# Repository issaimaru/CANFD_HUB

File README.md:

# CANFD_HUB
CANFDコントローラ「ひなた」用のハブ<br>
<br>

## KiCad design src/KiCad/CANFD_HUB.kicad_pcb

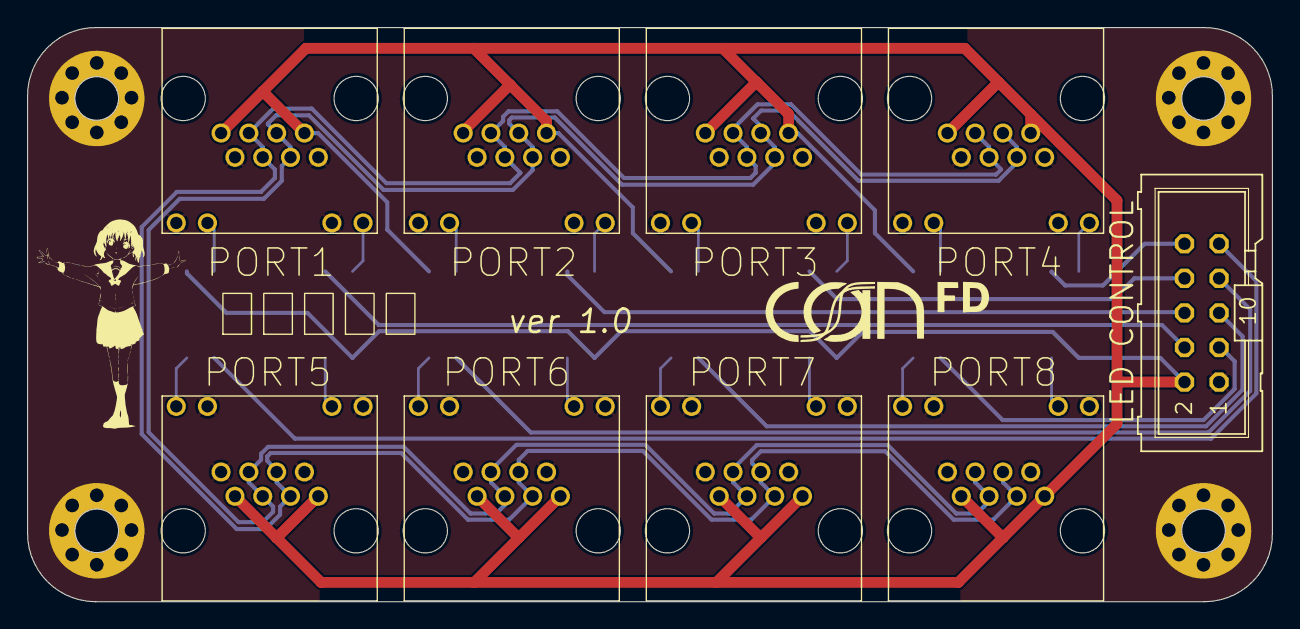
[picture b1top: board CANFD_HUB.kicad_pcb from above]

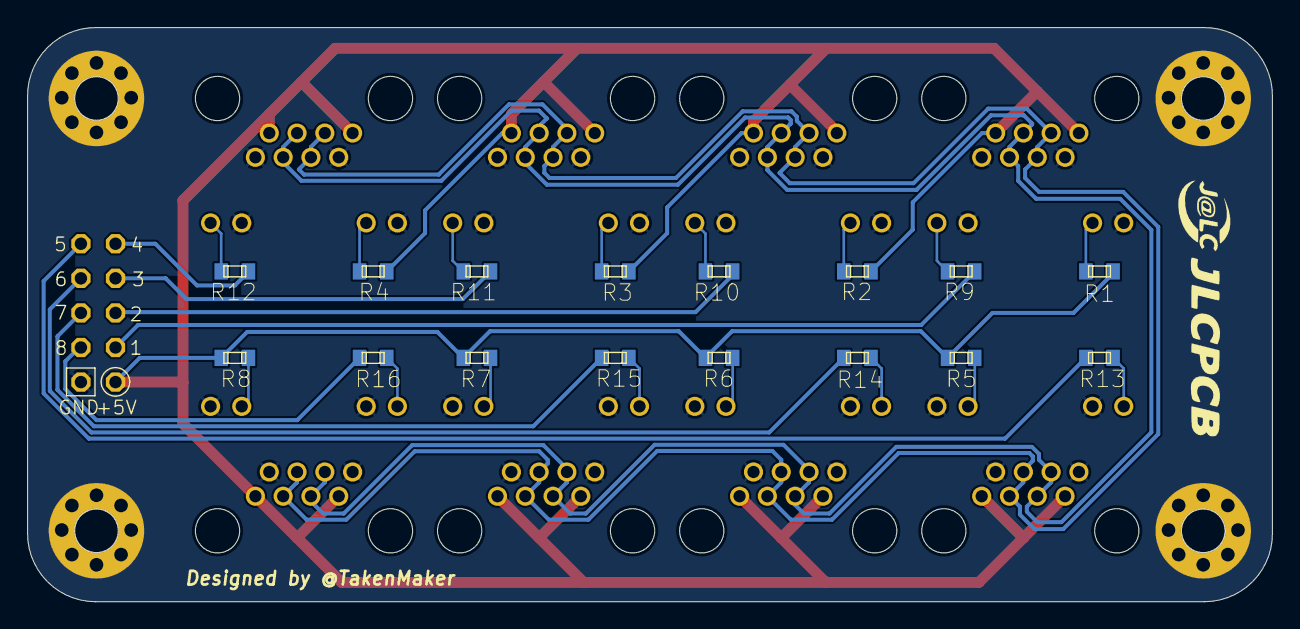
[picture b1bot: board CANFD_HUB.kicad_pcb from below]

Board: 2 copper layers, 91.4 x 42.2 mm, 29 parts (16 on the bottom side), 28 nets.

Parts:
H1, H2, H3, H4: MOUNT-HOLE3.2(NORESIST); 3,2
LED CONTROL: ML10
PORT1, PORT2, PORT3, PORT4, PORT5, PORT6, PORT7, PORT8: MTJ-88ARX1-LH
R1: R1; CR0603
R2: R2; CR0603
R3: R3; CR0603
R4: R4; CR0603
R5: R5; CR0603
R6: R6; CR0603
R7: R7; CR0603
R8: R8; CR0603
R9: R9; CR0603
R10: R10; CR0603
R11: R11; CR0603
R12: R12; CR0603
R13: R13; CR0603
R14: R14; CR0603
R15: R15; CR0603
R16: R16; CR0603

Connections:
+5V: LED CONTROL.2, PORT1.1, PORT1.7, PORT2.1, PORT2.7, PORT3.1, PORT3.7, PORT4.1, PORT4.7, PORT5.1, PORT5.7, PORT6.1, PORT6.7, PORT7.1, PORT7.7, PORT8.1, PORT8.7, R1.RIGHT, R2.RIGHT, R3.RIGHT, R4.RIGHT, R5.RIGHT, R6.RIGHT, R7.RIGHT, R8.RIGHT
CAN_H+: PORT1.5, PORT1.6, PORT2.5, PORT2.6, PORT3.5, PORT3.6, PORT4.5, PORT4.6, PORT5.5, PORT5.6, PORT6.5, PORT6.6, PORT7.5, PORT7.6, PORT8.5, PORT8.6
CAN_L-: PORT1.3, PORT1.4, PORT2.3, PORT2.4, PORT3.3, PORT3.4, PORT4.3, PORT4.4, PORT5.3, PORT5.4, PORT6.3, PORT6.4, PORT7.3, PORT7.4, PORT8.3, PORT8.4
GND: H1.P$1, H2.P$1, H3.P$1, H4.P$1, LED CONTROL.1, PORT1.2, PORT1.8, PORT1.LED1_K, PORT1.LED2_K, PORT2.2, PORT2.8, PORT2.LED1_K, PORT2.LED2_K, PORT3.2, PORT3.8, PORT3.LED1_K, PORT3.LED2_K, PORT4.2, PORT4.8, PORT4.LED1_K, PORT4.LED2_K, PORT5.2, PORT5.8, PORT5.LED1_K, PORT5.LED2_K, PORT6.2, PORT6.8, PORT6.LED1_K, PORT6.LED2_K, PORT7.2, PORT7.8, PORT7.LED1_K, PORT7.LED2_K, PORT8.2, PORT8.8, PORT8.LED1_K, PORT8.LED2_K
LED1: LED CONTROL.4, R9.LEFT
LED2: LED CONTROL.6, R10.LEFT
LED3: LED CONTROL.8, R11.LEFT
LED4: LED CONTROL.10, R12.LEFT
LED5: LED CONTROL.9, R13.LEFT
LED6: LED CONTROL.7, R14.LEFT
LED7: LED CONTROL.5, R15.LEFT
LED8: LED CONTROL.3, R16.LEFT
unnamed: PORT2.LED2_A, R2.LEFT
unnamed: PORT1.LED2_A, R1.LEFT
unnamed: PORT3.LED2_A, R3.LEFT
unnamed: PORT4.LED2_A, R4.LEFT
unnamed: PORT5.LED2_A, R5.LEFT
unnamed: PORT6.LED2_A, R6.LEFT
unnamed: PORT7.LED2_A, R7.LEFT
unnamed: PORT8.LED2_A, R8.LEFT
unnamed: PORT1.LED1_A, R9.RIGHT
unnamed: PORT2.LED1_A, R10.RIGHT
unnamed: PORT3.LED1_A, R11.RIGHT
unnamed: PORT4.LED1_A, R12.RIGHT
unnamed: PORT5.LED1_A, R13.RIGHT
unnamed: PORT6.LED1_A, R14.RIGHT
unnamed: PORT7.LED1_A, R15.RIGHT
unnamed: PORT8.LED1_A, R16.RIGHT

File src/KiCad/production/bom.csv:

Designator,Footprint,Quantity,Value,LCSC Part #
"H1, H2, H3, H4","3,2",4,MOUNT-HOLE3.2(NORESIST),
LED CONTROL,ML10,1,,
"PORT1, PORT2, PORT3, PORT4, PORT5, PORT6, PORT7, PORT8",MTJ-88ARX1-LH,8,MTJ-88ARX1-LH,
R1,CR0603,1,R1,
R10,CR0603,1,R10,
R11,CR0603,1,R11,
R12,CR0603,1,R12,
R13,CR0603,1,R13,
R14,CR0603,1,R14,
R15,CR0603,1,R15,
R16,CR0603,1,R16,
R2,CR0603,1,R2,
R3,CR0603,1,R3,
R4,CR0603,1,R4,
R5,CR0603,1,R5,
R6,CR0603,1,R6,
R7,CR0603,1,R7,
R8,CR0603,1,R8,
R9,CR0603,1,R9,

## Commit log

2023-06-15 [complete]sch
2023-06-16 [complete]CANFD_HUB
